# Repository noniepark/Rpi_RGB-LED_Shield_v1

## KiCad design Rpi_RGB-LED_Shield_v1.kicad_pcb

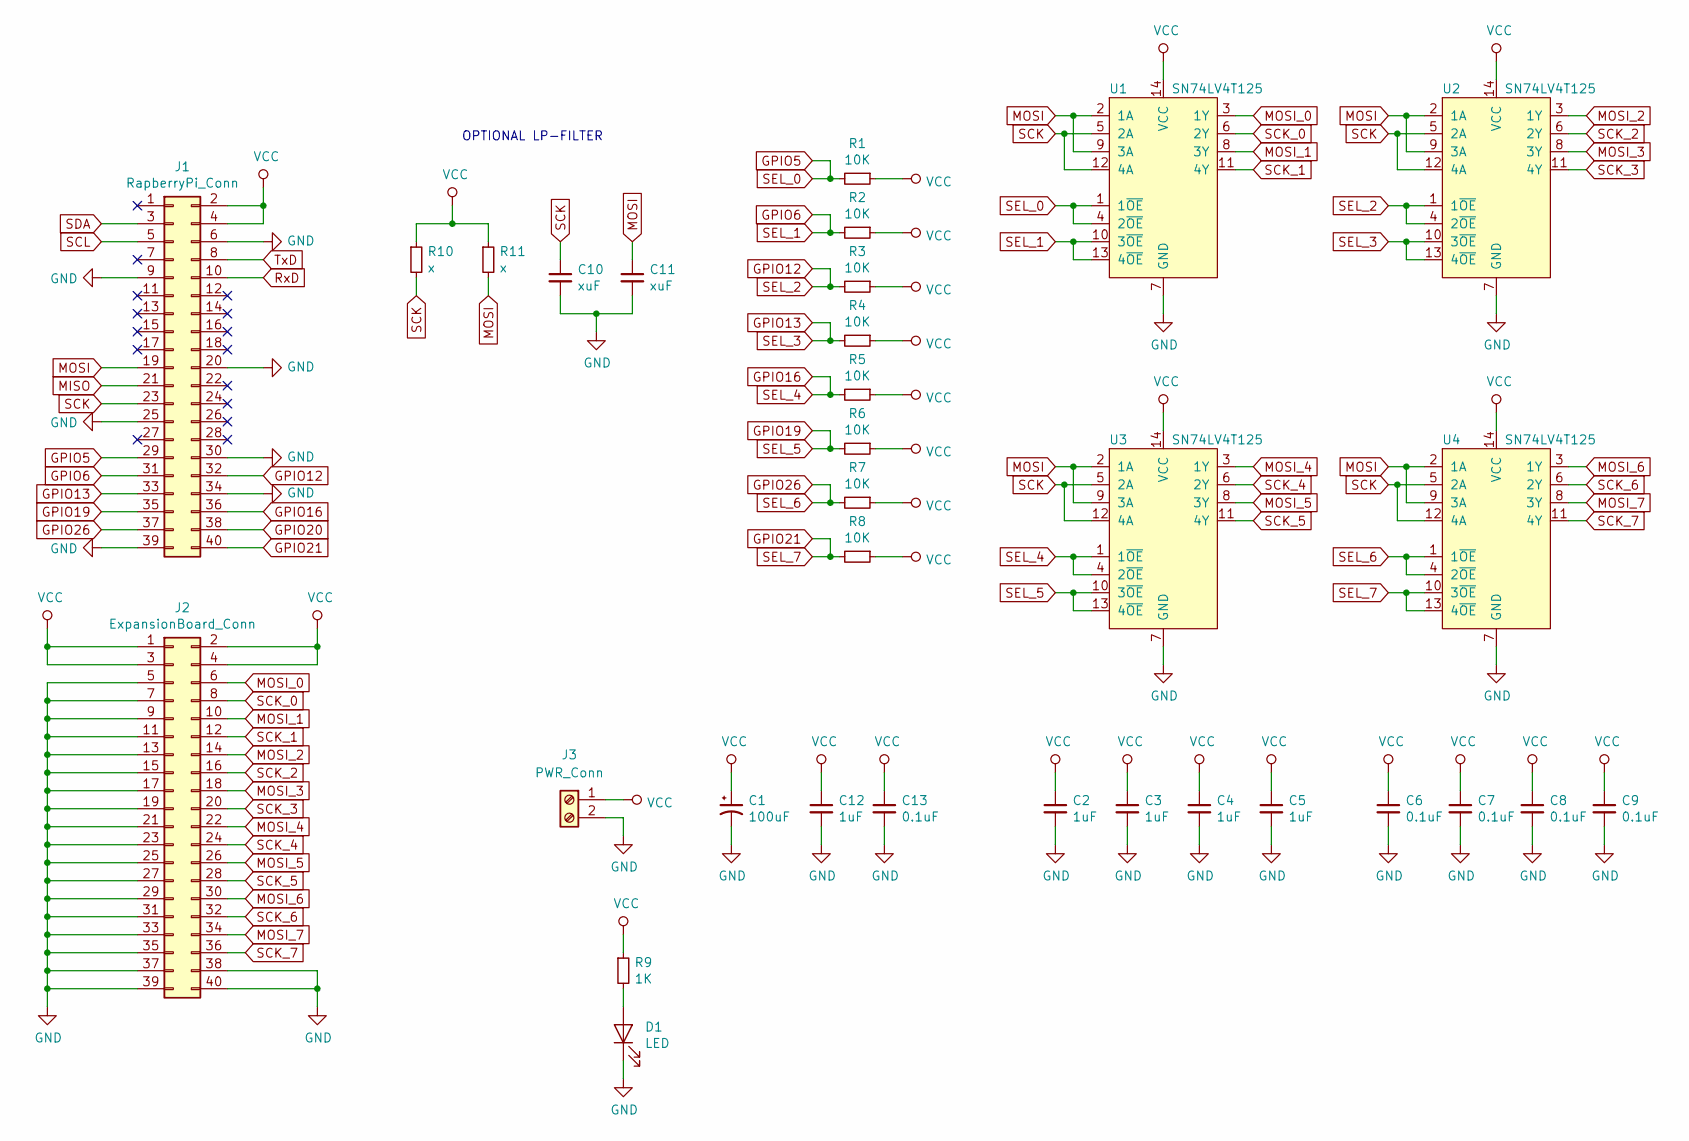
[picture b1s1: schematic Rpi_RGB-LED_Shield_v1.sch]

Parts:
C1: 100uF; C_Elec_6.3x5.4; MFG Part No. UWT1C101MCL1GB
C2, C3, C4, C5, C12: 1uF; C_0603_1608Metric
C6, C7, C8, C9, C13: 0.1uF; C_0603_1608Metric
C10, C11: xuF; C_0603_1608Metric
D1: LED; LED_0603_1608Metric
J1: RapberryPi_Conn; RPi_Hat
J2: ExpansionBoard_Conn; IDC-Header_2x20_P2.54mm_Vertical
J3: PWR_Conn; DINKLE_5EHDRC-2P; MFG Part No. 5EHDRC-2P
R1, R2, R3, R4, R5, R6, R7, R8: 10K; R_0603_1608Metric
R9: 1K; R_0603_1608Metric
R10, R11: x; R_0603_1608Metric
U1, U2, U3, U4: SN74LV4T125; TSSOP-14_4.4x5mm_P0.65mm

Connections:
GND: C1.2, C2.2, C3.2, C4.2, C5.2, C6.2, C7.2, C8.2, C9.2, C10.2, C11.2, C12.2, C13.2, D1.1 (K), J1.6, J1.9, J1.20, J1.25, J1.30, J1.34, J1.39, J2.5, J2.7, J2.9, J2.11, J2.13, J2.15, J2.17, J2.19, J2.21, J2.23, J2.25, J2.27, J2.29, J2.31, J2.33, J2.35, J2.37, J2.38, J2.39, J2.40, J3.2, U1.7 (GND), U2.7 (GND), U3.7 (GND), U4.7 (GND)
GPIO5: J1.29, R1.2, U1.1 (1~OE), U1.4 (2~OE)
GPIO6: J1.31, R2.2, U1.10 (3~OE), U1.13 (4~OE)
GPIO12: J1.32, R3.2, U2.1 (1~OE), U2.4 (2~OE)
GPIO13: J1.33, R4.2, U2.10 (3~OE), U2.13 (4~OE)
GPIO16: J1.36, R5.2, U3.1 (1~OE), U3.4 (2~OE)
GPIO19: J1.35, R6.2, U3.10 (3~OE), U3.13 (4~OE)
GPIO20: J1.38
GPIO21: J1.40, R8.2, U4.10 (3~OE), U4.13 (4~OE)
GPIO26: J1.37, R7.2, U4.1 (1~OE), U4.4 (2~OE)
MISO: J1.21
MOSI: C11.1, J1.19, R11.2, U1.2 (1A), U1.9 (3A), U2.2 (1A), U2.9 (3A), U3.2 (1A), U3.9 (3A), U4.2 (1A), U4.9 (3A)
MOSI_0: J2.6, U1.3 (1Y)
MOSI_1: J2.10, U1.8 (3Y)
MOSI_2: J2.14, U2.3 (1Y)
MOSI_3: J2.18, U2.8 (3Y)
MOSI_4: J2.22, U3.3 (1Y)
MOSI_5: J2.26, U3.8 (3Y)
MOSI_6: J2.30, U4.3 (1Y)
MOSI_7: J2.34, U4.8 (3Y)
unnamed: D1.2 (A), R9.2
RxD: J1.10
SCK: C10.1, J1.23, R10.2, U1.5 (2A), U1.12 (4A), U2.5 (2A), U2.12 (4A), U3.5 (2A), U3.12 (4A), U4.5 (2A), U4.12 (4A)
SCK_0: J2.8, U1.6 (2Y)
SCK_1: J2.12, U1.11 (4Y)
SCK_2: J2.16, U2.6 (2Y)
SCK_3: J2.20, U2.11 (4Y)
SCK_4: J2.24, U3.6 (2Y)
SCK_5: J2.28, U3.11 (4Y)
SCK_6: J2.32, U4.6 (2Y)
SCK_7: J2.36, U4.11 (4Y)
SCL: J1.5
SDA: J1.3
TxD: J1.8
VCC: C1.1, C2.1, C3.1, C4.1, C5.1, C6.1, C7.1, C8.1, C9.1, C12.1, C13.1, J1.2, J1.4, J2.1, J2.2, J2.3, J2.4, J3.1, R1.1, R2.1, R3.1, R4.1, R5.1, R6.1, R7.1, R8.1, R9.1, R10.1, R11.1, U1.14 (VCC), U2.14 (VCC), U3.14 (VCC), U4.14 (VCC)

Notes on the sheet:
OPTIONAL LP-FILTER

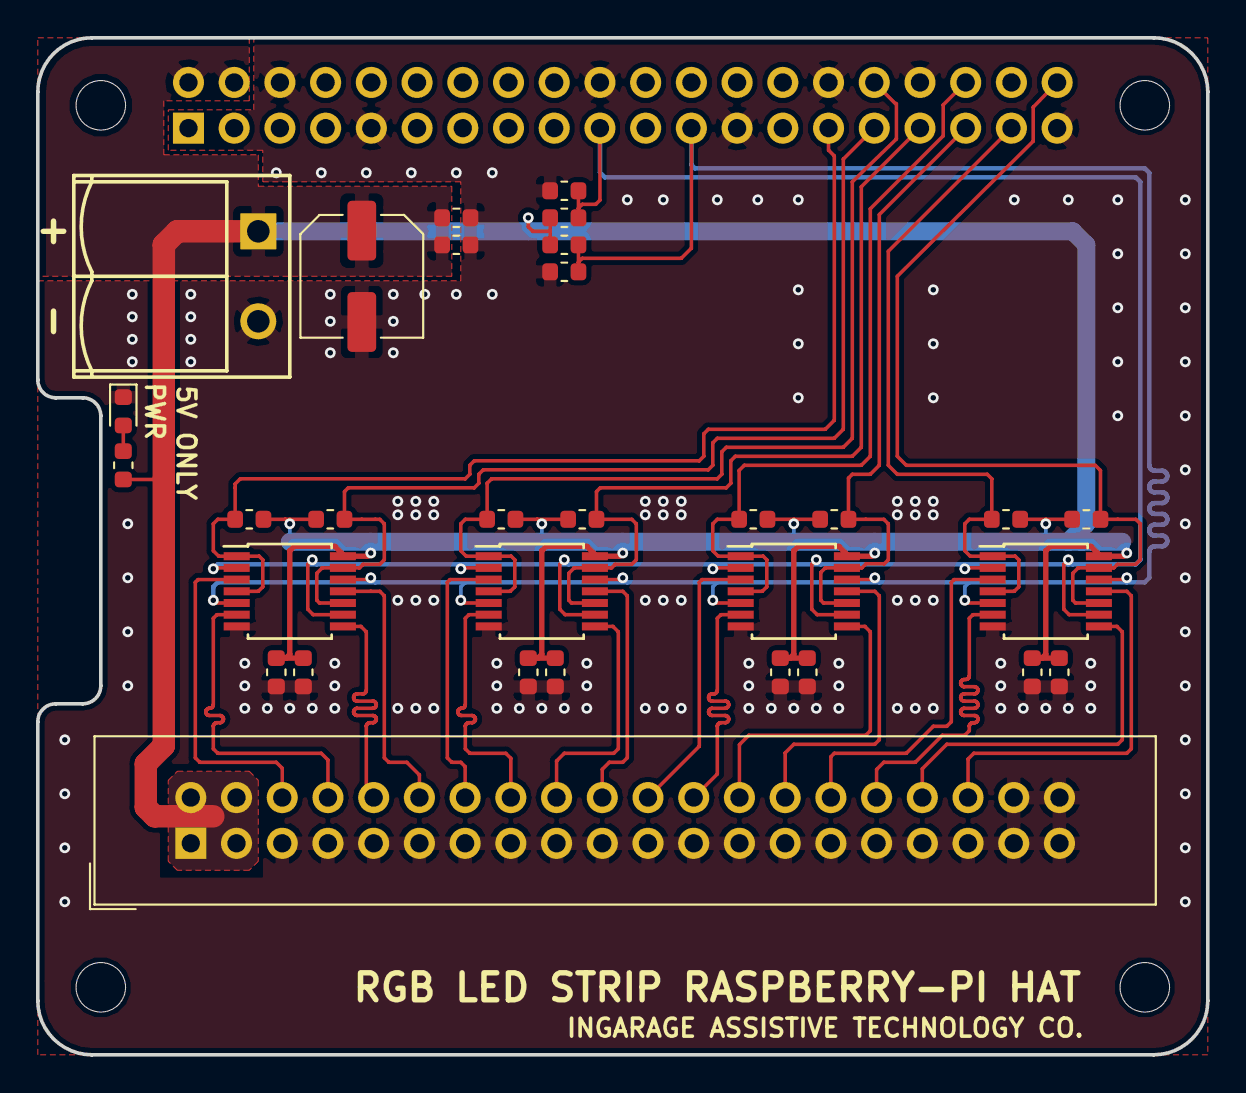
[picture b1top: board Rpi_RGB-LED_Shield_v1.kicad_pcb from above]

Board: 2 copper layers, 65.0 x 56.5 mm, 32 parts (0 on the bottom side), 29 nets.

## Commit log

2019-04-22 First commit.
2019-04-23 Put some progress
2019-04-25 Schematic complete
2019-04-25 Put come more progress
2019-04-26 Push more effort
2019-04-26 A little bit closer to the final
